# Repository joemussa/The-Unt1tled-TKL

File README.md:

# The-Unt1tled-TKL
Ten-Keyless Custom Keyboard (Title Pending... or not?)

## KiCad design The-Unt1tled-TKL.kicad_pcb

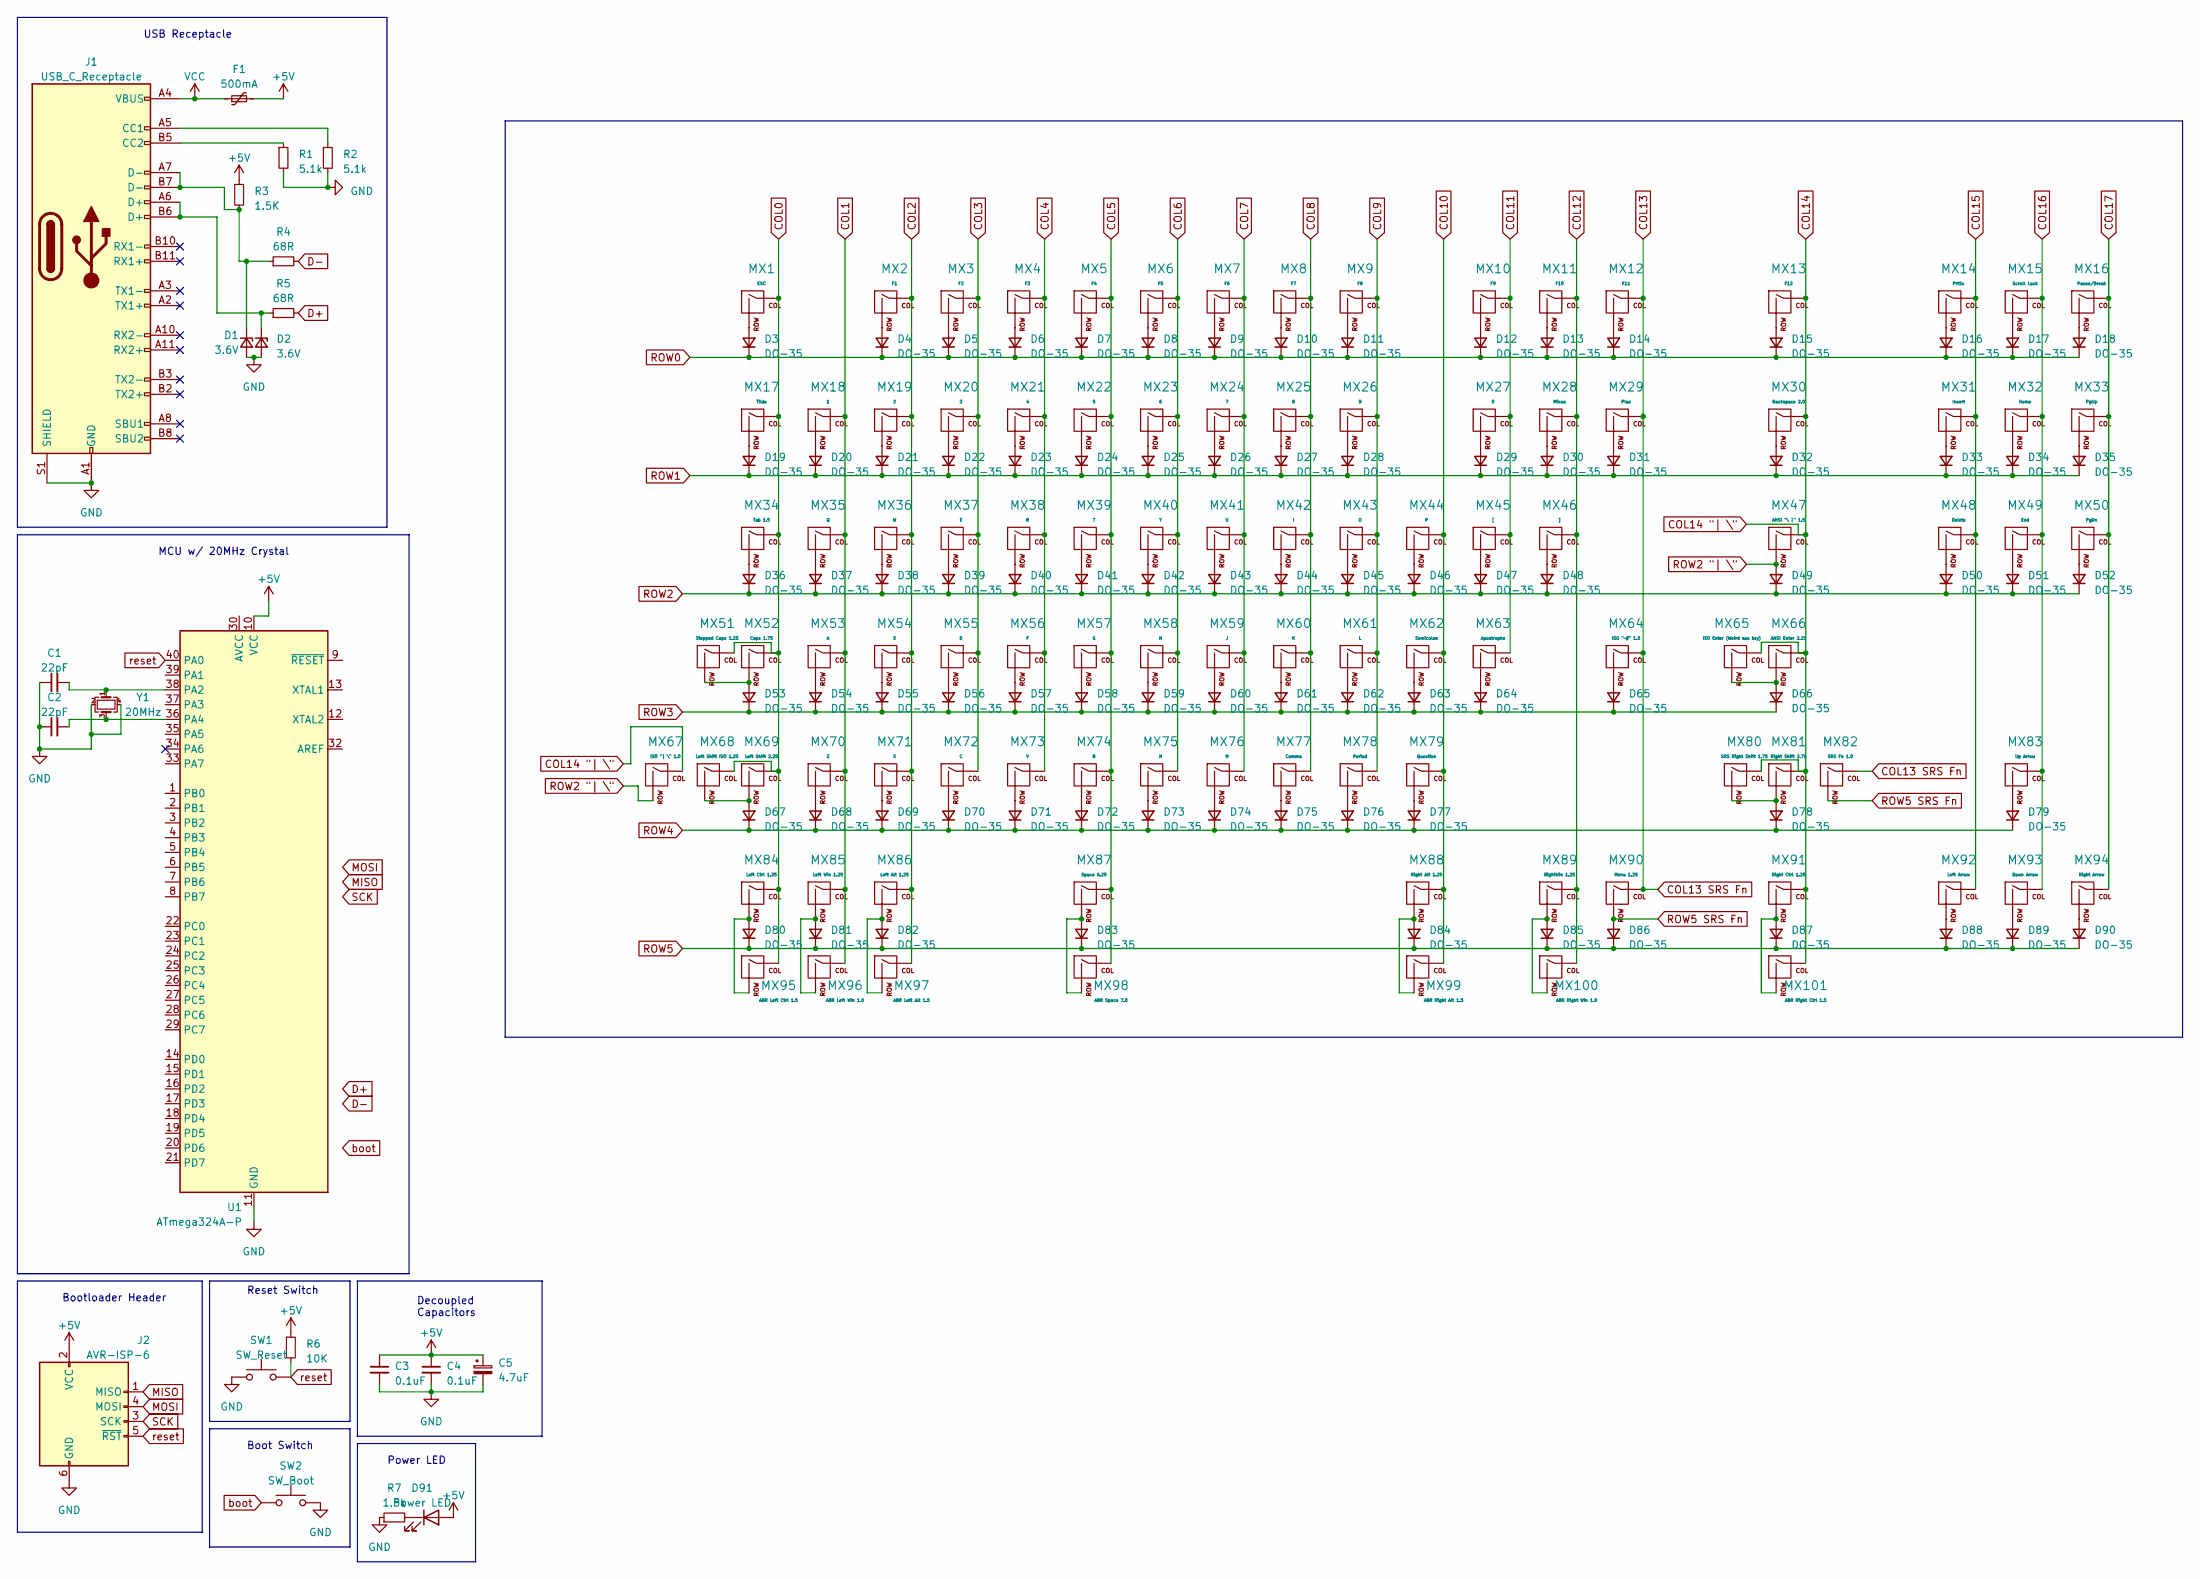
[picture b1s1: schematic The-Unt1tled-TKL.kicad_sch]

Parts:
C1, C2: 22pF; C_Disc_D5.0mm_W2.5mm_P2.50mm
C3, C4: 0.1uF; CP_Radial_D5.0mm_P2.00mm
C5: 4.7uF; CP_Radial_D5.0mm_P2.00mm
D1, D2: 3.6V; D_DO-35_SOD27_P7.62mm_Horizontal
D3, D4, D5, D6, D7, D8, D9, D10, D11, D12, D13, D14, D15, D16, D17, D18, D19, D20, D21, D22, D23, D24, D25, D26, D27, D28, D29, D30, D31, D32, D33, D34, D35, D36, D37, D38, D39, D40, D41, D42, D43, D44, D45, D46, D47, D48, D49, D50, D51, D52, D53, D54, D55, D56, D57, D58, D59, D60, D61, D62, D63, D64, D65, D66, D67, D68, D69, D70, D71, D72, D73, D74, D75, D76, D77, D78, D79, D80, D81, D82, D83, D84, D85, D86, D87, D88, D89, D90: DO-35; D_DO-35_SOD27_P7.62mm_Horizontal
D91: Power LED; LED_2010_5025Metric_Pad1.52x2.65mm_HandSolder
F1: 500mA; Fuse_1206_3216Metric
J1: USB_C_Receptacle; USB_C_Receptacle_Amphenol_12401548E4-2A
J2: AVR-ISP-6; IDC-Header_2x03_P2.54mm_Vertical
MX1: ESC; MXOnly-1U-NoLED
MX2: F1; MXOnly-1U-NoLED
MX3: F2; MXOnly-1U-NoLED
MX4: F3; MXOnly-1U-NoLED
MX5: F4; MXOnly-1U-NoLED
MX6: F5; MXOnly-1U-NoLED
MX7: F6; MXOnly-1U-NoLED
MX8: F7; MXOnly-1U-NoLED
MX9: F8; MXOnly-1U-NoLED
MX10: F9; MXOnly-1U-NoLED
MX11: F10; MXOnly-1U-NoLED
MX12: F11; MXOnly-1U-NoLED
MX13: F12; MXOnly-1U-NoLED
MX14: PrtSc; MXOnly-1U-NoLED
MX15: Scroll Lock; MXOnly-1U-NoLED
MX16: Pause/Break; MXOnly-1U-NoLED
MX17: Tilde; MXOnly-1U-NoLED
MX18: 1; MXOnly-1U-NoLED
MX19: 2; MXOnly-1U-NoLED
MX20: 3; MXOnly-1U-NoLED
MX21: 4; MXOnly-1U-NoLED
MX22: 5; MXOnly-1U-NoLED
MX23: 6; MXOnly-1U-NoLED
MX24: 7; MXOnly-1U-NoLED
MX25: 8; MXOnly-1U-NoLED
MX26: 9; MXOnly-1U-NoLED
MX27: 0; MXOnly-1U-NoLED
MX28: Minus; MXOnly-1U-NoLED
MX29: Plus; MXOnly-1U-NoLED
MX30: Backspace 2.0; MXOnly-2U-NoLED
MX31: Insert; MXOnly-1U-NoLED
MX32: Home; MXOnly-1U-NoLED
MX33: PgUp; MXOnly-1U-NoLED
MX34: Tab 1.5; MXOnly-1.5U-NoLED
MX35: Q; MXOnly-1U-NoLED
MX36: W; MXOnly-1U-NoLED
MX37: E; MXOnly-1U-NoLED
MX38: R; MXOnly-1U-NoLED
MX39: T; MXOnly-1U-NoLED
MX40: Y; MXOnly-1U-NoLED
MX41: U; MXOnly-1U-NoLED
MX42: I; MXOnly-1U-NoLED
MX43: O; MXOnly-1U-NoLED
MX44: P; MXOnly-1U-NoLED
MX45: [; MXOnly-1U-NoLED
MX46: ]; MXOnly-1U-NoLED
MX47: ANSI "\ |" 1.5; MXOnly-1.5U-NoLED
MX48: Delete; MXOnly-1U-NoLED
MX49: End; MXOnly-1U-NoLED
MX50: PgDn; MXOnly-1U-NoLED
MX51: Stepped Caps 1.25; MXOnly-1.25U-NoLED
MX52: Caps 1.75; MXOnly-1.75U-NoLED
MX53: A; MXOnly-1U-NoLED
MX54: S; MXOnly-1U-NoLED
MX55: D; MXOnly-1U-NoLED
MX56: F; MXOnly-1U-NoLED
MX57: G; MXOnly-1U-NoLED
MX58: H; MXOnly-1U-NoLED
MX59: J; MXOnly-1U-NoLED
MX60: K; MXOnly-1U-NoLED
MX61: L; MXOnly-1U-NoLED
MX62: Semicolon; MXOnly-1U-NoLED
MX63: Apostrophe; MXOnly-1U-NoLED
MX64: ISO "~#" 1.0; MXOnly-1U-NoLED
MX65: ISO Enter (Weird ass key); MXOnly-ISO-NoLED
MX66: ANSI Enter 2.25; MXOnly-2.25U-NoLED
MX67: ISO "| \" 1.0; MXOnly-1U-NoLED
MX68: Left Shift ISO 1.25; MXOnly-1.25U-NoLED
MX69: Left Shift 2.25; MXOnly-2.25U-NoLED
MX70: Z; MXOnly-1U-NoLED
MX71: X; MXOnly-1U-NoLED
MX72: C; MXOnly-1U-NoLED
MX73: V; MXOnly-1U-NoLED
MX74: B; MXOnly-1U-NoLED
MX75: N; MXOnly-1U-NoLED
MX76: M; MXOnly-1U-NoLED
MX77: Comma; MXOnly-1U-NoLED
MX78: Period; MXOnly-1U-NoLED
MX79: Question; MXOnly-1U-NoLED
MX80: SRS Right Shift 1.75; MXOnly-1.75U-NoLED
MX81: Right Shift 2.75; MXOnly-2.75U-NoLED
MX82: SRS Fn 1.0; MXOnly-1U-NoLED
MX83: Up Arrow; MXOnly-1U-NoLED
MX84: Left Ctrl 1.25; MXOnly-1.25U-NoLED
MX85: Left Win 1.25; MXOnly-1.25U-NoLED
MX86: Left Alt 1.25; MXOnly-1.25U-NoLED
MX87: Space 6.25; MXOnly-6.25U-NoLED
MX88: Right Alt 1.25; MXOnly-1.25U-NoLED
MX89: RightWin 1.25; MXOnly-1.25U-NoLED
MX90: Menu 1.25; MXOnly-1.25U-NoLED
MX91: Right Ctrl 1.25; MXOnly-1.25U-NoLED
MX92: Left Arrow; MXOnly-1U-NoLED
MX93: Down Arrow; MXOnly-1U-NoLED
MX94: Right Arrow; MXOnly-1U-NoLED
MX95: ABR Left Ctrl 1.5; MXOnly-1.5U-NoLED
MX96: ABR Left Win 1.0; MXOnly-1U-NoLED
MX97: ABR Left Alt 1.5; MXOnly-1.5U-NoLED
MX98: ABR Space 7.0; MXOnly-7U-NoLED
MX99: ABR Right Alt 1.5; MXOnly-1.5U-NoLED
MX100: ABR Right Win 1.0; MXOnly-1U-NoLED
MX101: ABR Right Ctrl 1.5; MXOnly-1.5U-NoLED
R1, R2: 5.1k; R_Axial_DIN0207_L6.3mm_D2.5mm_P7.62mm_Horizontal
R3: 1.5K; R_Axial_DIN0207_L6.3mm_D2.5mm_P7.62mm_Horizontal
R4, R5: 68R; R_Axial_DIN0207_L6.3mm_D2.5mm_P7.62mm_Horizontal
R6: 10K; R_Axial_DIN0207_L6.3mm_D2.5mm_P7.62mm_Horizontal
R7: 1.5k; R_Axial_DIN0207_L6.3mm_D2.5mm_P7.62mm_Horizontal
SW1: SW_Reset; SKQG-1155865
SW2: SW_Boot; SKQG-1155865
U1: ATmega324A-P; DIP-40_W15.24mm_Socket_LongPads
Y1: 20MHz; Crystal_SMD_3225-4Pin_3.2x2.5mm

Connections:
+5V: C3.1, C4.1, C5.1, D91.2 (A), F1.2, J2.2 (VCC), R3.1, R6.1, U1.10 (VCC)
COL0: MX1.1 (COL), MX17.1 (COL), MX34.1 (COL), MX51.1 (COL), MX52.1 (COL), MX68.1 (COL), MX69.1 (COL), MX84.1 (COL), MX95.1 (COL)
COL1: MX18.1 (COL), MX35.1 (COL), MX53.1 (COL), MX70.1 (COL), MX85.1 (COL), MX96.1 (COL)
COL2: MX2.1 (COL), MX19.1 (COL), MX36.1 (COL), MX54.1 (COL), MX71.1 (COL), MX86.1 (COL), MX97.1 (COL)
COL3: MX3.1 (COL), MX20.1 (COL), MX37.1 (COL), MX55.1 (COL), MX72.1 (COL)
COL4: MX4.1 (COL), MX21.1 (COL), MX38.1 (COL), MX56.1 (COL), MX73.1 (COL)
COL5: MX5.1 (COL), MX22.1 (COL), MX39.1 (COL), MX57.1 (COL), MX74.1 (COL), MX87.1 (COL), MX98.1 (COL)
COL6: MX6.1 (COL), MX23.1 (COL), MX40.1 (COL), MX58.1 (COL), MX75.1 (COL)
COL7: MX7.1 (COL), MX24.1 (COL), MX41.1 (COL), MX59.1 (COL), MX76.1 (COL)
COL8: MX8.1 (COL), MX25.1 (COL), MX42.1 (COL), MX60.1 (COL), MX77.1 (COL)
COL9: MX9.1 (COL), MX26.1 (COL), MX43.1 (COL), MX61.1 (COL), MX78.1 (COL)
COL10: MX44.1 (COL), MX62.1 (COL), MX79.1 (COL), MX88.1 (COL), MX99.1 (COL)
COL11: MX10.1 (COL), MX27.1 (COL), MX45.1 (COL), MX63.1 (COL)
COL12: MX11.1 (COL), MX28.1 (COL), MX46.1 (COL), MX89.1 (COL), MX100.1 (COL)
COL13: MX12.1 (COL), MX29.1 (COL), MX64.1 (COL), MX82.1 (COL), MX90.1 (COL)
COL14: MX13.1 (COL), MX30.1 (COL), MX47.1 (COL), MX65.1 (COL), MX66.1 (COL), MX67.1 (COL), MX80.1 (COL), MX81.1 (COL), MX91.1 (COL), MX101.1 (COL)
COL15: MX14.1 (COL), MX31.1 (COL), MX48.1 (COL), MX92.1 (COL)
COL16: MX15.1 (COL), MX32.1 (COL), MX49.1 (COL), MX83.1 (COL), MX93.1 (COL)
COL17: MX16.1 (COL), MX33.1 (COL), MX50.1 (COL), MX94.1 (COL)
D+: R5.2
D-: R4.2
GND: C1.1, C2.1, C3.2, C4.2, C5.2, D1.2 (A), D2.2 (A), J1.A1 (GND), J1.A12 (GND), J1.B1 (GND), J1.B12 (GND), J1.S1 (SHIELD), J2.6 (GND), R1.2, R2.2, R7.1, SW1.1, SW2.2, U1.11 (GND), U1.31 (GND), Y1.2, Y1.4
MISO: J2.1 (MISO)
MOSI: J2.4 (MOSI)
unnamed: D1.1 (K), J1.A7 (D-), J1.B7 (D-), R3.2, R4.1
unnamed: D2.1 (K), J1.A6 (D+), J1.B6 (D+), R5.1
unnamed: D3.2 (A), MX1.2 (ROW)
unnamed: D4.2 (A), MX2.2 (ROW)
unnamed: D5.2 (A), MX3.2 (ROW)
unnamed: D6.2 (A), MX4.2 (ROW)
unnamed: D7.2 (A), MX5.2 (ROW)
unnamed: D8.2 (A), MX6.2 (ROW)
unnamed: D9.2 (A), MX7.2 (ROW)
unnamed: D10.2 (A), MX8.2 (ROW)
unnamed: D11.2 (A), MX9.2 (ROW)
unnamed: D12.2 (A), MX10.2 (ROW)
unnamed: D13.2 (A), MX11.2 (ROW)
unnamed: D14.2 (A), MX12.2 (ROW)
unnamed: D15.2 (A), MX13.2 (ROW)
unnamed: D16.2 (A), MX14.2 (ROW)
unnamed: D17.2 (A), MX15.2 (ROW)
unnamed: D18.2 (A), MX16.2 (ROW)
unnamed: D19.2 (A), MX17.2 (ROW)
unnamed: D20.2 (A), MX18.2 (ROW)
unnamed: D21.2 (A), MX19.2 (ROW)
unnamed: D22.2 (A), MX20.2 (ROW)
unnamed: D23.2 (A), MX21.2 (ROW)
unnamed: D24.2 (A), MX22.2 (ROW)
unnamed: D25.2 (A), MX23.2 (ROW)
unnamed: D26.2 (A), MX24.2 (ROW)
unnamed: D27.2 (A), MX25.2 (ROW)
unnamed: D28.2 (A), MX26.2 (ROW)
unnamed: D29.2 (A), MX27.2 (ROW)
unnamed: D30.2 (A), MX28.2 (ROW)
unnamed: D31.2 (A), MX29.2 (ROW)
unnamed: D32.2 (A), MX30.2 (ROW)
unnamed: D33.2 (A), MX31.2 (ROW)
unnamed: D34.2 (A), MX32.2 (ROW)
unnamed: D35.2 (A), MX33.2 (ROW)
unnamed: D36.2 (A), MX34.2 (ROW)
unnamed: D37.2 (A), MX35.2 (ROW)
unnamed: D38.2 (A), MX36.2 (ROW)
unnamed: D39.2 (A), MX37.2 (ROW)
unnamed: D40.2 (A), MX38.2 (ROW)
unnamed: D41.2 (A), MX39.2 (ROW)
unnamed: D42.2 (A), MX40.2 (ROW)
unnamed: D43.2 (A), MX41.2 (ROW)
unnamed: D44.2 (A), MX42.2 (ROW)
unnamed: D45.2 (A), MX43.2 (ROW)
unnamed: D46.2 (A), MX44.2 (ROW)
unnamed: D47.2 (A), MX45.2 (ROW)
unnamed: D48.2 (A), MX46.2 (ROW)
unnamed: D50.2 (A), MX48.2 (ROW)
unnamed: D51.2 (A), MX49.2 (ROW)
unnamed: D52.2 (A), MX50.2 (ROW)
unnamed: D53.2 (A), MX51.2 (ROW), MX52.2 (ROW)
unnamed: D54.2 (A), MX53.2 (ROW)
unnamed: D55.2 (A), MX54.2 (ROW)
unnamed: D56.2 (A), MX55.2 (ROW)
unnamed: D57.2 (A), MX56.2 (ROW)
unnamed: D58.2 (A), MX57.2 (ROW)
unnamed: D59.2 (A), MX58.2 (ROW)
unnamed: D60.2 (A), MX59.2 (ROW)
unnamed: D61.2 (A), MX60.2 (ROW)
unnamed: D62.2 (A), MX61.2 (ROW)
unnamed: D63.2 (A), MX62.2 (ROW)
unnamed: D64.2 (A), MX63.2 (ROW)
unnamed: D65.2 (A), MX64.2 (ROW)
unnamed: D66.2 (A), MX65.2 (ROW), MX66.2 (ROW)
unnamed: D67.2 (A), MX68.2 (ROW), MX69.2 (ROW)
unnamed: D68.2 (A), MX70.2 (ROW)
unnamed: D69.2 (A), MX71.2 (ROW)
unnamed: D70.2 (A), MX72.2 (ROW)
unnamed: D71.2 (A), MX73.2 (ROW)
unnamed: D72.2 (A), MX74.2 (ROW)
unnamed: D73.2 (A), MX75.2 (ROW)
unnamed: D74.2 (A), MX76.2 (ROW)
unnamed: D75.2 (A), MX77.2 (ROW)
unnamed: D76.2 (A), MX78.2 (ROW)
unnamed: D77.2 (A), MX79.2 (ROW)
unnamed: D78.2 (A), MX80.2 (ROW), MX81.2 (ROW)
unnamed: D79.2 (A), MX83.2 (ROW)
unnamed: D80.2 (A), MX84.2 (ROW), MX95.2 (ROW)
unnamed: D81.2 (A), MX85.2 (ROW), MX96.2 (ROW)
unnamed: D82.2 (A), MX86.2 (ROW), MX97.2 (ROW)
unnamed: D83.2 (A), MX87.2 (ROW), MX98.2 (ROW)
unnamed: D84.2 (A), MX88.2 (ROW), MX99.2 (ROW)
unnamed: D85.2 (A), MX89.2 (ROW), MX100.2 (ROW)
unnamed: D87.2 (A), MX91.2 (ROW), MX101.2 (ROW)
unnamed: D88.2 (A), MX92.2 (ROW)
unnamed: D89.2 (A), MX93.2 (ROW)
unnamed: D90.2 (A), MX94.2 (ROW)
unnamed: D91.1 (K), R7.2
unnamed: J1.A5 (CC1), R2.1
unnamed: J1.B5 (CC2), R1.1
unnamed: C1.2, U1.38 (PA2), Y1.1
unnamed: C2.2, U1.36 (PA4), Y1.3
ROW0: D3.1 (K), D4.1 (K), D5.1 (K), D6.1 (K), D7.1 (K), D8.1 (K), D9.1 (K), D10.1 (K), D11.1 (K), D12.1 (K), D13.1 (K), D14.1 (K), D15.1 (K), D16.1 (K), D17.1 (K), D18.1 (K)
ROW1: D19.1 (K), D20.1 (K), D21.1 (K), D22.1 (K), D23.1 (K), D24.1 (K), D25.1 (K), D26.1 (K), D27.1 (K), D28.1 (K), D29.1 (K), D30.1 (K), D31.1 (K), D32.1 (K), D33.1 (K), D34.1 (K), D35.1 (K)
ROW2: D36.1 (K), D37.1 (K), D38.1 (K), D39.1 (K), D40.1 (K), D41.1 (K), D42.1 (K), D43.1 (K), D44.1 (K), D45.1 (K), D46.1 (K), D47.1 (K), D48.1 (K), D49.1 (K), D50.1 (K), D51.1 (K), D52.1 (K)
ROW2 "| \": D49.2 (A), MX47.2 (ROW), MX67.2 (ROW)
ROW3: D53.1 (K), D54.1 (K), D55.1 (K), D56.1 (K), D57.1 (K), D58.1 (K), D59.1 (K), D60.1 (K), D61.1 (K), D62.1 (K), D63.1 (K), D64.1 (K), D65.1 (K), D66.1 (K)
ROW4: D67.1 (K), D68.1 (K), D69.1 (K), D70.1 (K), D71.1 (K), D72.1 (K), D73.1 (K), D74.1 (K), D75.1 (K), D76.1 (K), D77.1 (K), D78.1 (K), D79.1 (K)
ROW5: D80.1 (K), D81.1 (K), D82.1 (K), D83.1 (K), D84.1 (K), D85.1 (K), D86.1 (K), D87.1 (K), D88.1 (K), D89.1 (K), D90.1 (K)
ROW5 SRS Fn: D86.2 (A), MX82.2 (ROW), MX90.2 (ROW)
SCK: J2.3 (SCK)
VCC: F1.1, J1.A4 (VBUS), J1.A9 (VBUS), J1.B4 (VBUS), J1.B9 (VBUS)
boot: SW2.1
reset: J2.5 (~RST), R6.2, SW1.2, U1.40 (PA0)

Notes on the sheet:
Reset Switch
Boot Switch
Bootloader Header
MCU w/ 20MHz Crystal
Decoupled Capacitors
USB Receptacle
Power LED

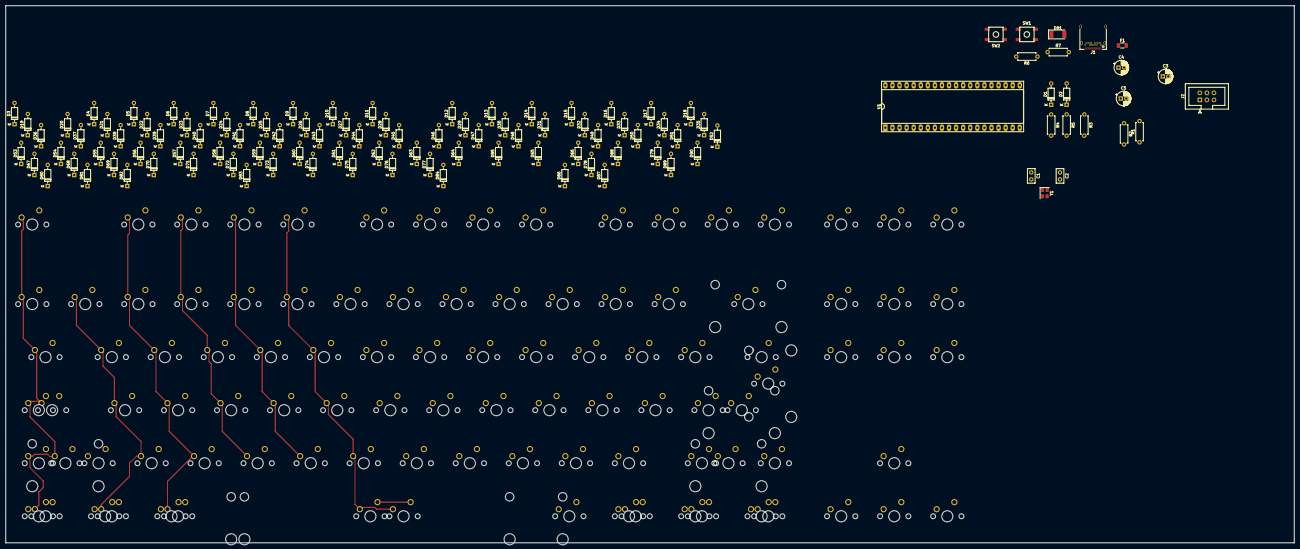
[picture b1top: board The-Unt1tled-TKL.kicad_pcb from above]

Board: 2 copper layers, 462.8 x 192.9 mm, 211 parts (0 on the bottom side), 123 nets.

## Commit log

2023-04-10 Initialized Project
    Initialized project
2023-04-10 Added submodules
2023-04-10 Added symbol and footprint libraries
    Added symbol and footprint libraries to KiCad project specific libraries.
2023-04-11 Schematic changes (TODO)
    Made schematic changes. Still have to fix footprint on keys.
2023-04-12 Re-did Whole Schematic
    I redesigned the whole PCB schematic to support ISO and ANSI. I also changed the microcontroller to one with more pins for row/col layout. Instead I'm using an ATmega324A-P. This requires the use of 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
2023-04-12 Fuck PCB Grid Editor
    I'm gonna put a bullet in my head.
2023-04-14 Many things
    - Figured out grid placement
    - Working on part placements
    - Changed footprint from MX-Alp Hybrid to MX-Only.
2023-04-14 Part placement and wireing
    Placed diodes. Still need to place other parts in their final position. Started wiring.
